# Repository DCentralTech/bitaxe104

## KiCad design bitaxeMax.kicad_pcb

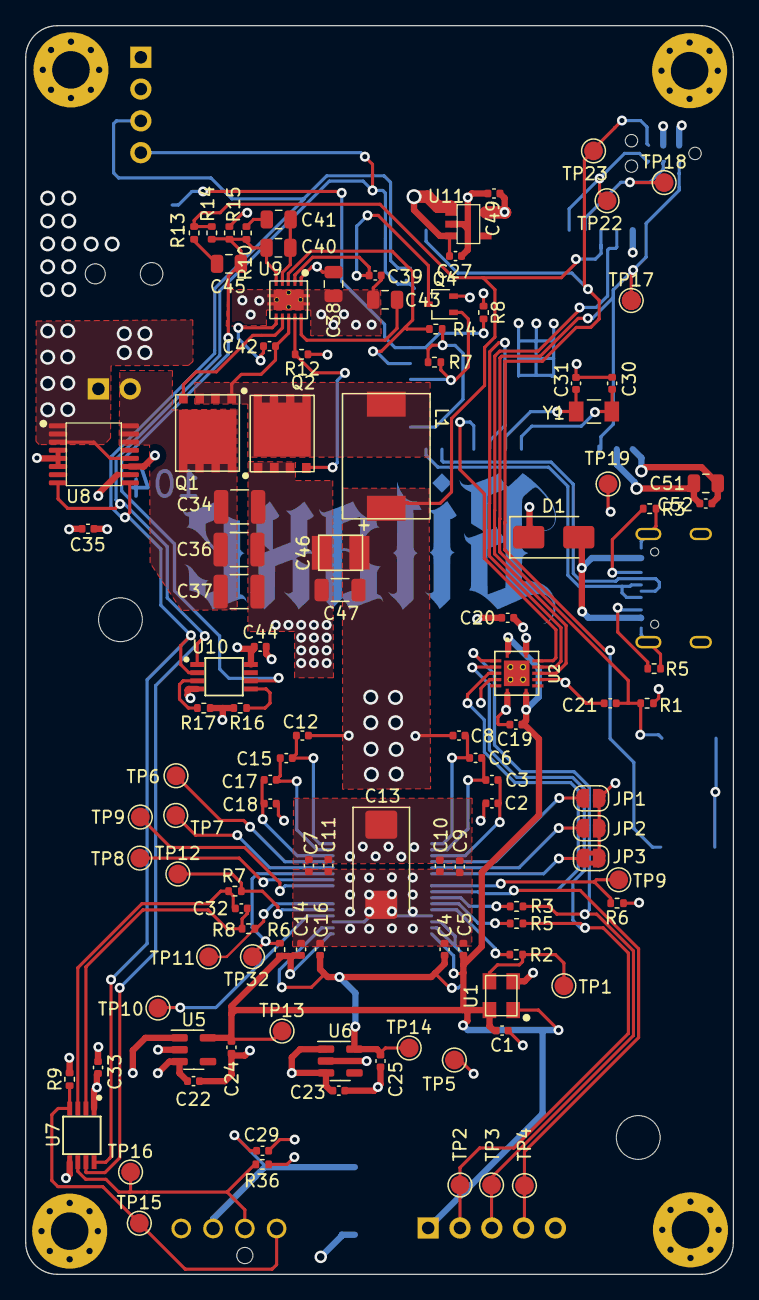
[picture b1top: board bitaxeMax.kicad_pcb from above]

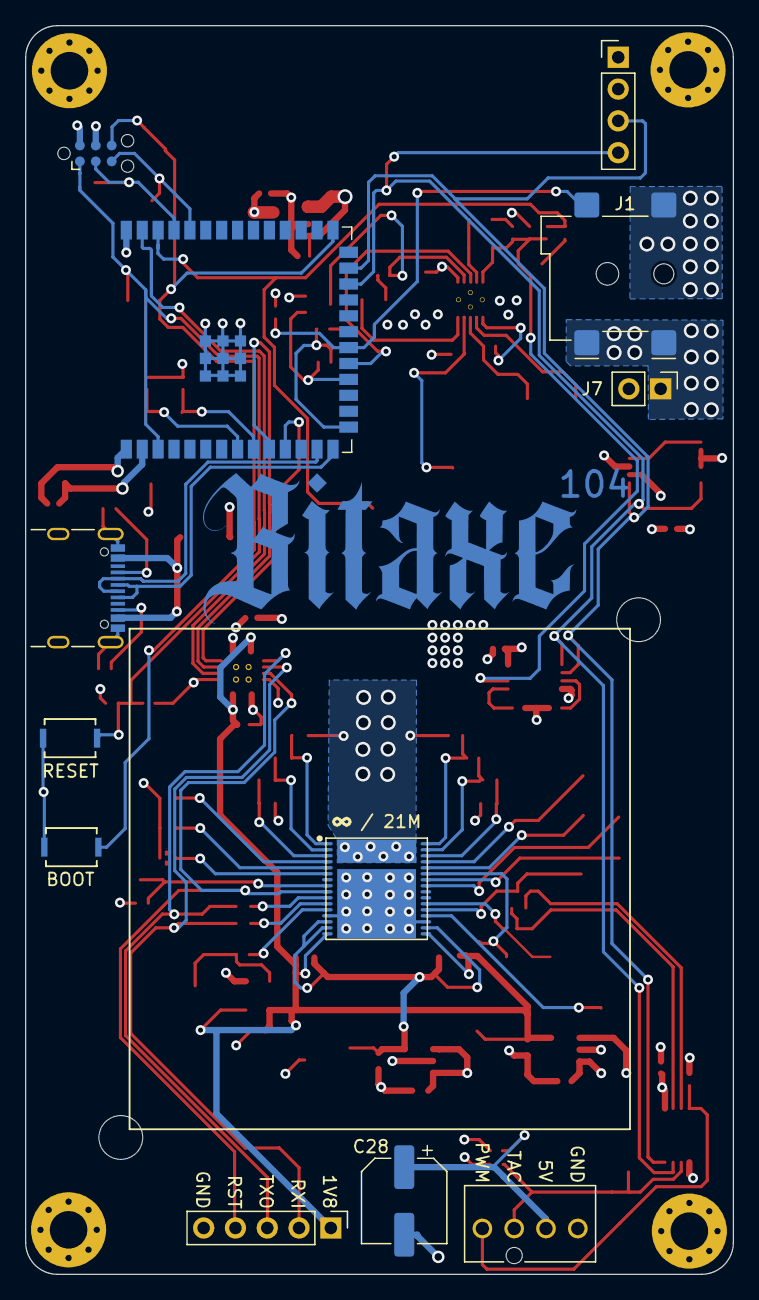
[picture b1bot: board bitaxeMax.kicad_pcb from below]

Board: 4 copper layers, 56.5 x 99.8 mm, 129 parts (12 on the bottom side), 68 nets.

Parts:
C1, C7, C9, C19, C20, C22, C23, C29, C33, C42, C52: 0.1uF; C_0402_1005Metric
C2, C3, C4, C5, C6, C8, C10, C11, C12, C14, C15, C16, C17, C18, C21, C24, C25, C27, C35, C44, C49: 1uF; C_0402_1005Metric
C13: 330uF; CP_EIA-7343-31_Kemet-D_Pad2.25x2.55mm_HandSolder
C28: 220uF; CP_Elec_6.3x7.7
C30, C31: 6.8pF; C_0402_1005Metric
C32: 470pF; C_0402_1005Metric
C34, C36, C37: 47uF; C_1210_3225Metric
C38: 1uF; C_0805_2012Metric
C39: 3.3nF; C_0402_1005Metric
C40: 180pF; C_0805_2012Metric
C41: 1.5nF; C_0805_2012Metric
C43, C51: 10uF; C_0805_2012Metric
C45: 470pF; C_0805_2012Metric
C46: 220uF; CAP_2R5TPE220MAFB
C47: 100uF; C_1206_3216Metric
D1: SS310; D_SMA
H1, H2, H3, H4: AlignmentHole; MountingHole_3mm_Pad_Via
H5, H6: MountingHole; MountingHole_3.5mm
IC1: BM1397_mode1; BM1397
J1: 54-00164; BarrelJack_Wuerth_694106106102_2.0x5.5mm
J3: Conn_01x05; PinHeader_1x05_P2.54mm_Vertical
J4: Conn_01x04; 470531000
J5: TC2030-IDC; Tag-Connect_TC2030-IDC-NL_2x03_P1.27mm_Vertical
J7: Conn_01x02; PinHeader_1x02_P2.54mm_Vertical
J8: USB_C_Receptacle_USB2.0; USB_C_Receptacle_GCT_USB4105-xx-A_16P_TopMnt_Horizontal
J9: Conn_01x04; PinHeader_1x04_P2.54mm_Vertical
JP1, JP2: SolderJumper_2_Open; SolderJumper-2_P1.3mm_Open_RoundedPad1.0x1.5mm
JP3: SolderJumper_2_Bridged; SolderJumper-2_P1.3mm_Bridged2Bar_RoundedPad1.0x1.5mm
L1: 150nH; FP1005R1-R15-R
Q1, Q2: CSD17311Q5
Q4: 2N7002K; SOT-323_SC-70
R1, R4, R6, R6#2, R7, R9, R36: 10k; R_0402_1005Metric
R2, R3, R5#2: 0; R_0402_1005Metric
R3#2, R5: 5.1k; R_0402_1005Metric
R7#2, R8#2: 100; R_0402_1005Metric
R8: 1M; R_0402_1005Metric
R10: 3.83k; R_0402_1005Metric
R12: 4.12k; R_0402_1005Metric
R13: 1.33k; R_0402_1005Metric
R14: 4.99k; R_0402_1005Metric
R15: 3.32k; R_0402_1005Metric
R16: 80k; R_0402_1005Metric
R17: DNP; R_0402_1005Metric
SW1, SW2: GT-TC029B-H025-L1N; SW_CS1213AGF260_CRS
TP1, TP2, TP3, TP4, TP5, TP6, TP7, TP8, TP9, TP9#2, TP10, TP11, TP12, TP13, TP14, TP15, TP16, TP17, TP18, TP19, TP22, TP23, TP32: TestPoint; TestPoint_Pad_D1.5mm
U1: 25MHz; O 25,0-JO32-B-1V3-1-T1-LF
U2: TXB0104RGYR; TXB0104
U5, U6: MCP1824; SOT-23-5
U7: EMC2101; TSSOP-8_3x3mm_P0.65mm
U8: INA260; TSSOP-16_4.4x5mm_P0.65mm
U9: TPS40305
U10: DS4432U+; TSSOP-8_3x3mm_P0.65mm
U11: RT9080-33GJ5
U12: ESP32-S3-WROOM-1
Y1: 32.768kHz; SC32S-7PF20PPM

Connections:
/3V3: C20.1, C33.1, C35.1, C44.1, C49.1, C51.1, C52.1, J5.2, J9.2, R1.1, R4.1, R7.1, R8.1, R9.2, R36.2, TP19.1, U2.14 (VCCB), U7.1 (VDD), U8.10 (VS), U10.8 (VCC), U11.5 (VOUT), U12.2 (3V3), U12.15 (GPIO3/TOUCH3/ADC1_CH2*)
/5V: C22.1, C23.1, C27.1, C28.1, C29.1, C34.1, C36.1, C37.1, C38.1, D1.1, J4.2, J7.2, Q1.5 (D), U5.1 (VIN), U5.3 (EN), U6.1 (VIN), U6.3 (EN), U8.14 (IN-), U8.15 (IN-), U8.16 (IN-), U9.1 (VDD), U11.1 (VIN), U11.3 (EN)
/BM1397/0V8: C4.1, C16.1, C25.1, IC1.14 (PLL_VDD), IC1.15 (VDDIO_08_0), IC1.18 (VDDIO_08_1), TP14.1, U6.5 (VOUT)
/BM1397/1V8: C1.2, C5.1, C14.1, C19.1, C24.1, IC1.16 (VDDIO_18_0), IC1.17 (VDDIO_18_1), J3.1, R6#2.2, TP13.1, U1.1 (EN), U1.4 (VIN), U2.1 (VCCA), U2.8 (OE), U5.5 (VOUT)
/BM1397/BM_BI: IC1.8 (BI), R6.2, TP9.1
/BM1397/BM_CLKI: IC1.12 (CLKI), R2.2
/BM1397/CI: J3.2, R5#2.1, TP2.1, U2.3 (A2)
/BM1397/RO: J3.3, R3.1, TP3.1, U2.2 (A1)
/BM1397/RST_N: IC1.9 (NRSTI), J3.4, TP4.1, U2.4 (A3)
/ESP32/EN: C21.1, J5.1, R1.2, SW1.2, TP17.1, U12.3 (EN)
/ESP32/IO0: J5.6, SW2.2, TP23.1, U12.27 (GPIO0/BOOT*)
/ESP32/P_RX: J5.5, TP22.1, U12.36 (U0RXD/GPIO44/CLK_OUT2)
/ESP32/P_TX: J5.3, TP18.1, U12.37 (U0TXD/GPIO43/CLK_OUT1)
/ESP32/XIN32: C30.1, U12.8 (GPIO15/U0RTS/ADC2_CH4/XTAL_32K_P), Y1.1
/ESP32/XOUT32: C31.1, U12.9 (GPIO16/U0CTS/ADC2_CH5/XTAL_32K_NH5), Y1.2
/Fan/FAN_PWM: J4.4, R9.1, TP15.1, U7.4 (FAN)
/Fan/FAN_TACH: J4.3, R36.1, TP16.1, U7.6 (ALERT/TACH)
/Power/OUT0: C40.2, C45.2, R10.2, R14.2, R15.1, U9.5 (FB), U10.6 (OUT0)
/Power/PGOOD: R4.2, U9.3 (PGOOD), U12.19 (GPIO11/TOUCH11/ADC2_CH0/FSPID/FSPIIO5/S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)
/Power/SW: C42.2, L1.1, Q1.1, Q1.2, Q1.3 (S), Q2.5 (D), U9.8 (SW)
/Power/VIN: J1.1, J7.1, U8.1 (IN+), U8.2 (IN+), U8.3 (IN+), U8.12 (VBUS)
/RST: U2.11 (B3), U12.39 (GPIO1/TOUCH1/ADC1_CH0)
/RX: U2.13 (B1), U12.11 (GPIO18/U1RXD/ADC2_CH7/CLK_OUT3)
/SCL: J9.3, U7.8 (SMCLK), U8.9 (SCL), U10.2 (SCL), U12.25 (GPIO48/SPICLK_N/SUBSPICLK_N_DIFF)
/SDA: J9.4, U7.7 (SMDATA), U8.8 (SDA), U10.1 (SDA), U12.24 (GPIO47/SPICLK_P/SUBSPICLK_P_DIFF)
/TEMP_N: IC1.21 (TEMP_N), R7#2.2, TP12.1
/TEMP_P: IC1.22 (TEMP_P), R8#2.1, TP11.1
/TX: U2.12 (B2), U12.10 (GPIO17/U1TXD/ADC2_CH6)
/VDD: C7.1, C8.2, C9.1, C10.1, C11.1, C12.1, C13.1, C46.1, C47.1, IC1.33 (VDD), L1.2, R13.1, R14.1, U12.38 (GPIO2/TOUCH2/ADC1_CH1)
GND: C1.1, C2.1, C4.2, C5.2, C7.2, C9.2, C10.2, C11.2, C13.2, C14.2, C16.2, C18.2, C19.2, C20.2, C21.2, C22.2, C23.2, C24.2, C25.2, C27.2, C28.2, C29.2, C30.2, C31.2, C33.2, C34.2, C35.2, C36.2, C37.2, C38.2, C39.2, C43.2, C44.2, C46.2, C47.2, C49.2, C51.2, C52.2, IC1.13 (PLL_VSS), IC1.19 (VSS), IC1.34 (VSS_0), J1.2, J3.5, J4.1, J5.4, J8.A1 (GND), J8.A12 (GND), J8.B1 (GND), J8.B12 (GND), J8.S1 (SHIELD), J9.1, JP1.1 (A), JP2.1 (A), JP3.1 (A), Q2.1, Q2.2, Q2.3 (S), Q4.2 (S), R3#2.1, R5.1, R6.1, R12.2, R15.2, R16.2, R17.2, SW1.1, SW2.1, TP5.1, U1.2 (GND), U2.5 (A4), U2.7 (GND), U2.10 (B4), U2.15 (GND), U2.16 (GND), U2.17 (GND), U2.18 (GND), U2.19 (GND), U5.2 (GND), U6.2 (GND), U7.5 (GND), U8.4 (A1), U8.5 (A0), U8.6 (GND), U8.11 (GND), U9.11 (GND), U10.4 (GND), U11.2 (GND), U12.1 (GND), U12.40 (GND), U12.41 (GND)
NET-(J8-CC1): J8.A5 (CC1), R3#2.2
unnamed: C2.2, C3.1, IC1.3 (VDD1_0)
unnamed: C3.2, C6.1, IC1.2 (VDD2_0)
unnamed: C6.2, C8.1, IC1.1 (VDD3_0)
unnamed: C12.2, C15.1, IC1.32 (VDD3_1)
unnamed: C15.2, C17.1, IC1.31 (VDD2_1)
unnamed: C17.2, C18.1, IC1.30 (VDD1_1)
unnamed: C32.1, R8#2.2, U7.2 (DP)
unnamed: C32.2, R7#2.1, U7.3 (DN)
unnamed: C40.1, C41.1, U9.4 (COMP)
unnamed: C41.2, R10.1
unnamed: C42.1, U9.6 (BOOT)
unnamed: C43.1, U9.10 (BP)
unnamed: C45.1, R13.2
unnamed: D1.2, J8.A4 (VBUS), J8.A9 (VBUS), J8.B4 (VBUS), J8.B9 (VBUS)
unnamed: IC1.4 (ADDR0), JP1.2 (B)
unnamed: IC1.5 (ADDR1), JP2.2 (B)
unnamed: IC1.6 (ADDR2), JP3.2 (B)
unnamed: IC1.10 (RO), R3.2
unnamed: IC1.11 (CI), R5#2.2
unnamed: IC1.20 (PIN_MODE), TP10.1
unnamed: IC1.25 (CLKO), TP9#2.1
unnamed: IC1.26 (CO), TP8.1
unnamed: IC1.27 (RI), R6#2.1, TP32.1
unnamed: IC1.28 (NRSTO), TP7.1
unnamed: IC1.29 (BO), TP6.1
unnamed: J8.B5 (CC2), R5.2
unnamed: Q1.4 (G), U9.7 (HDRV)
unnamed: Q2.4 (G), R12.1, U9.9 (LDRV)
unnamed: C39.1, Q4.3 (D), U9.2 (SS)
unnamed: R2.1, TP1.1, U1.3 (OUT)
unnamed: R16.1, U10.5 (FS0)
unnamed: R17.1, U10.3 (FS1)
unnamed: J8.A7 (D-), J8.B7 (D-), U12.13 (GPIO19/U1RTS/ADC2_CH8/CLK_OUT2/USB_D-)
unnamed: J8.A6 (D+), J8.B6 (D+), U12.14 (GPIO20/U1CTS/ADC2_CH9/CLK_OUT1/USB_D+)
PLUG_SENSE: J1.3, R8.2, U12.20 (GPIO12/TOUCH12/ADC2_CH1/FSPICLK/FSPIIO6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)
PWR_EN: Q4.1 (G), R7.2, U12.18 (GPIO10/TOUCH10/ADC1_CH9/FSPICS0/FSPIIO4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)
x: U2.6, U2.9, U11.4
